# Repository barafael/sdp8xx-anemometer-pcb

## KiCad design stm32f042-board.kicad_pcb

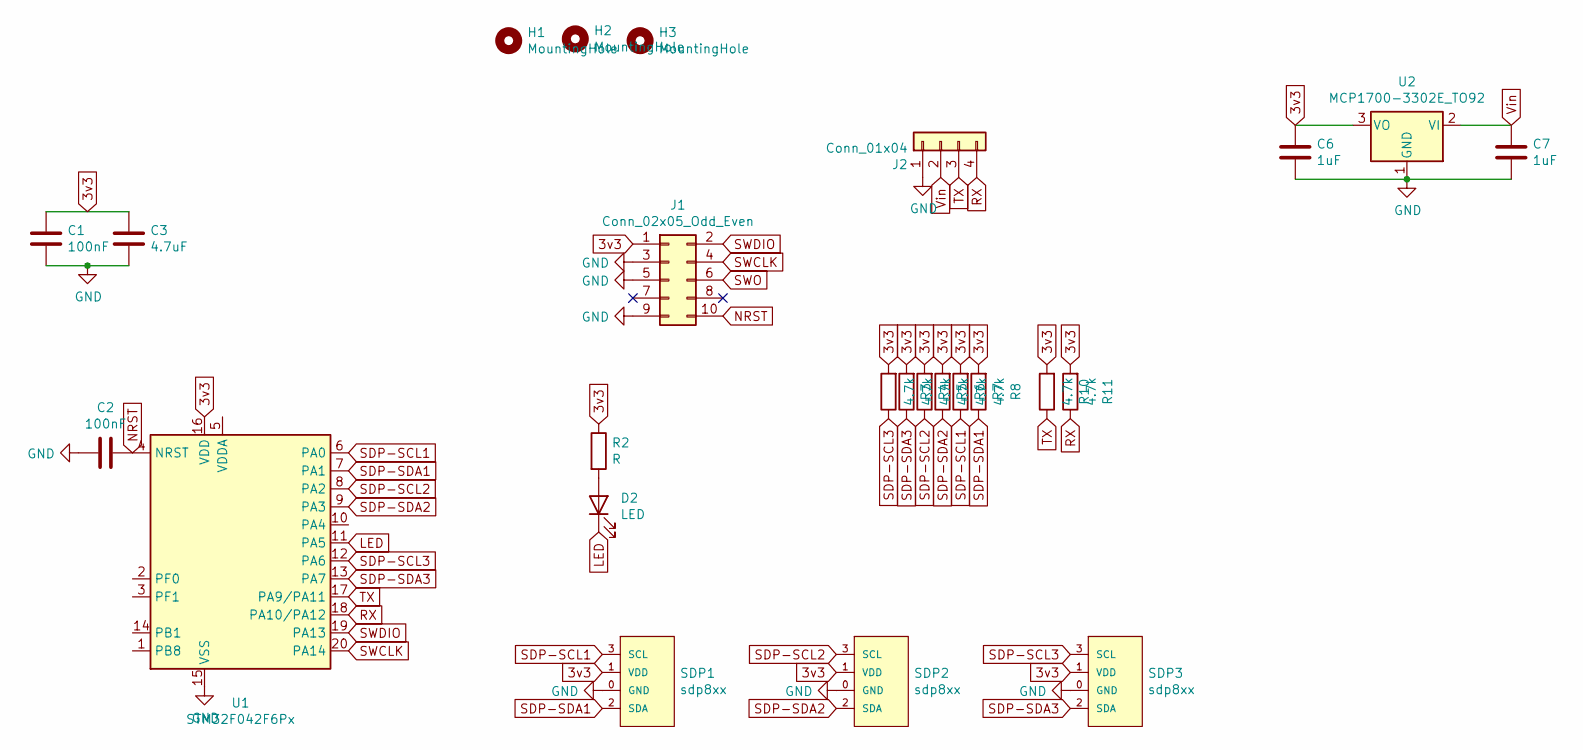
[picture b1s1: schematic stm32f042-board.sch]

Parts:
C1, C2: 100nF; C_0603_1608Metric_Pad1.08x0.95mm_HandSolder
C3: 4.7uF; C_0603_1608Metric_Pad1.08x0.95mm_HandSolder
C6, C7: 1uF; C_0603_1608Metric_Pad1.08x0.95mm_HandSolder
D2: LED; D_0805_2012Metric_Pad1.15x1.40mm_HandSolder
H1, H2, H3: MountingHole; MountingHole_2.1mm
J1: Conn_02x05_Odd_Even; PinHeader_2x05_P1.27mm_Vertical
J2: Conn_01x04; PinHeader_1x04_P2.54mm_Vertical
R2: R; R_0805_2012Metric
R3, R4, R5, R6, R7, R8, R10, R11: 4.7k; R_0805_2012Metric_Pad1.20x1.40mm_HandSolder
SDP1, SDP2, SDP3: sdp8xx
U1: STM32F042F6Px; TSSOP-20_4.4x6.5mm_P0.65mm
U2: MCP1700-3302E_TO92; TO-92_Inline

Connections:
3v3: C1.1, C3.1, C6.1, J1.1, R2.1, R3.2, R4.2, R5.2, R6.2, R7.2, R8.2, R10.2, R11.2, SDP1.1 (VDD), SDP2.1 (VDD), SDP3.1 (VDD), U1.16 (VDD), U2.3 (VO)
GND: C1.2, C2.2, C3.2, C6.2, C7.2, J1.3, J1.5, J1.9, J2.1, SDP1.0 (GND), SDP2.0 (GND), SDP3.0 (GND), U1.15 (VSS), U2.1 (GND)
LED: D2.1 (K), U1.11 (PA5)
NRST: C2.1, J1.10, U1.4 (NRST)
unnamed: D2.2 (A), R2.2
RX: J2.4, R11.1, U1.18 (PA10/PA12)
SDP-SCL1: R7.1, SDP1.3 (SCL), U1.6 (PA0)
SDP-SCL2: R5.1, SDP2.3 (SCL), U1.8 (PA2)
SDP-SCL3: R3.1, SDP3.3 (SCL), U1.12 (PA6)
SDP-SDA1: R8.1, SDP1.2 (SDA), U1.7 (PA1)
SDP-SDA2: R6.1, SDP2.2 (SDA), U1.9 (PA3)
SDP-SDA3: R4.1, SDP3.2 (SDA), U1.13 (PA7)
SWCLK: J1.4, U1.20 (PA14)
SWDIO: J1.2, U1.19 (PA13)
SWO: J1.6
TX: J2.3, R10.1, U1.17 (PA9/PA11)
Vin: C7.1, J2.2, U2.2 (VI)

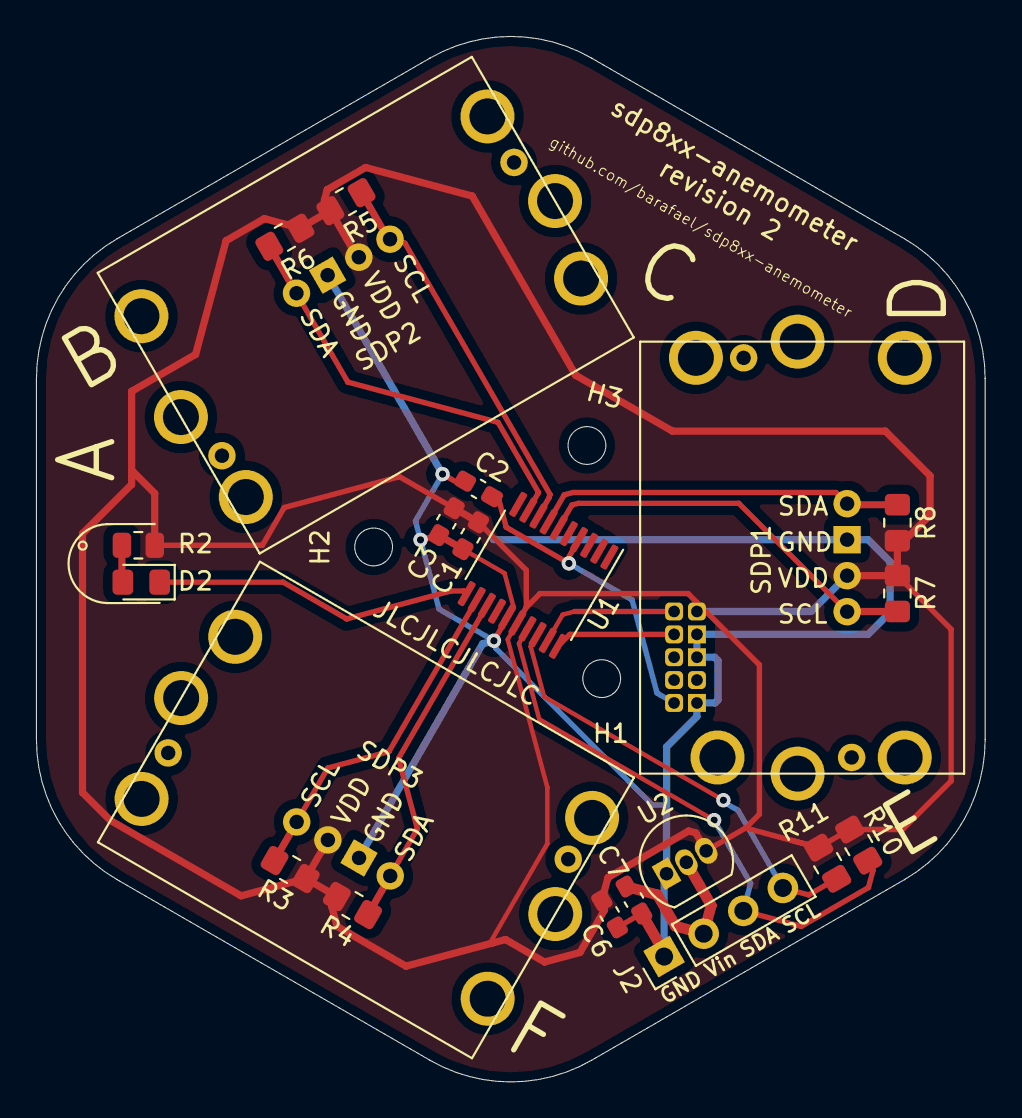
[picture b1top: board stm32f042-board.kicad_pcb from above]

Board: 2 copper layers, 52.7 x 58.1 mm, 25 parts (1 on the bottom side), 16 nets.

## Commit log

2021-01-12 Add sdp8xx symbol and footprint
2021-01-12 Fix paths
2021-01-12 Update footprint
2021-01-12 Update footprints
2021-01-17 Update board
2021-02-03 Update PCB
2021-02-03 Add images
2021-02-22 Remove unneeded features and remove size
2021-02-23 Make connections
